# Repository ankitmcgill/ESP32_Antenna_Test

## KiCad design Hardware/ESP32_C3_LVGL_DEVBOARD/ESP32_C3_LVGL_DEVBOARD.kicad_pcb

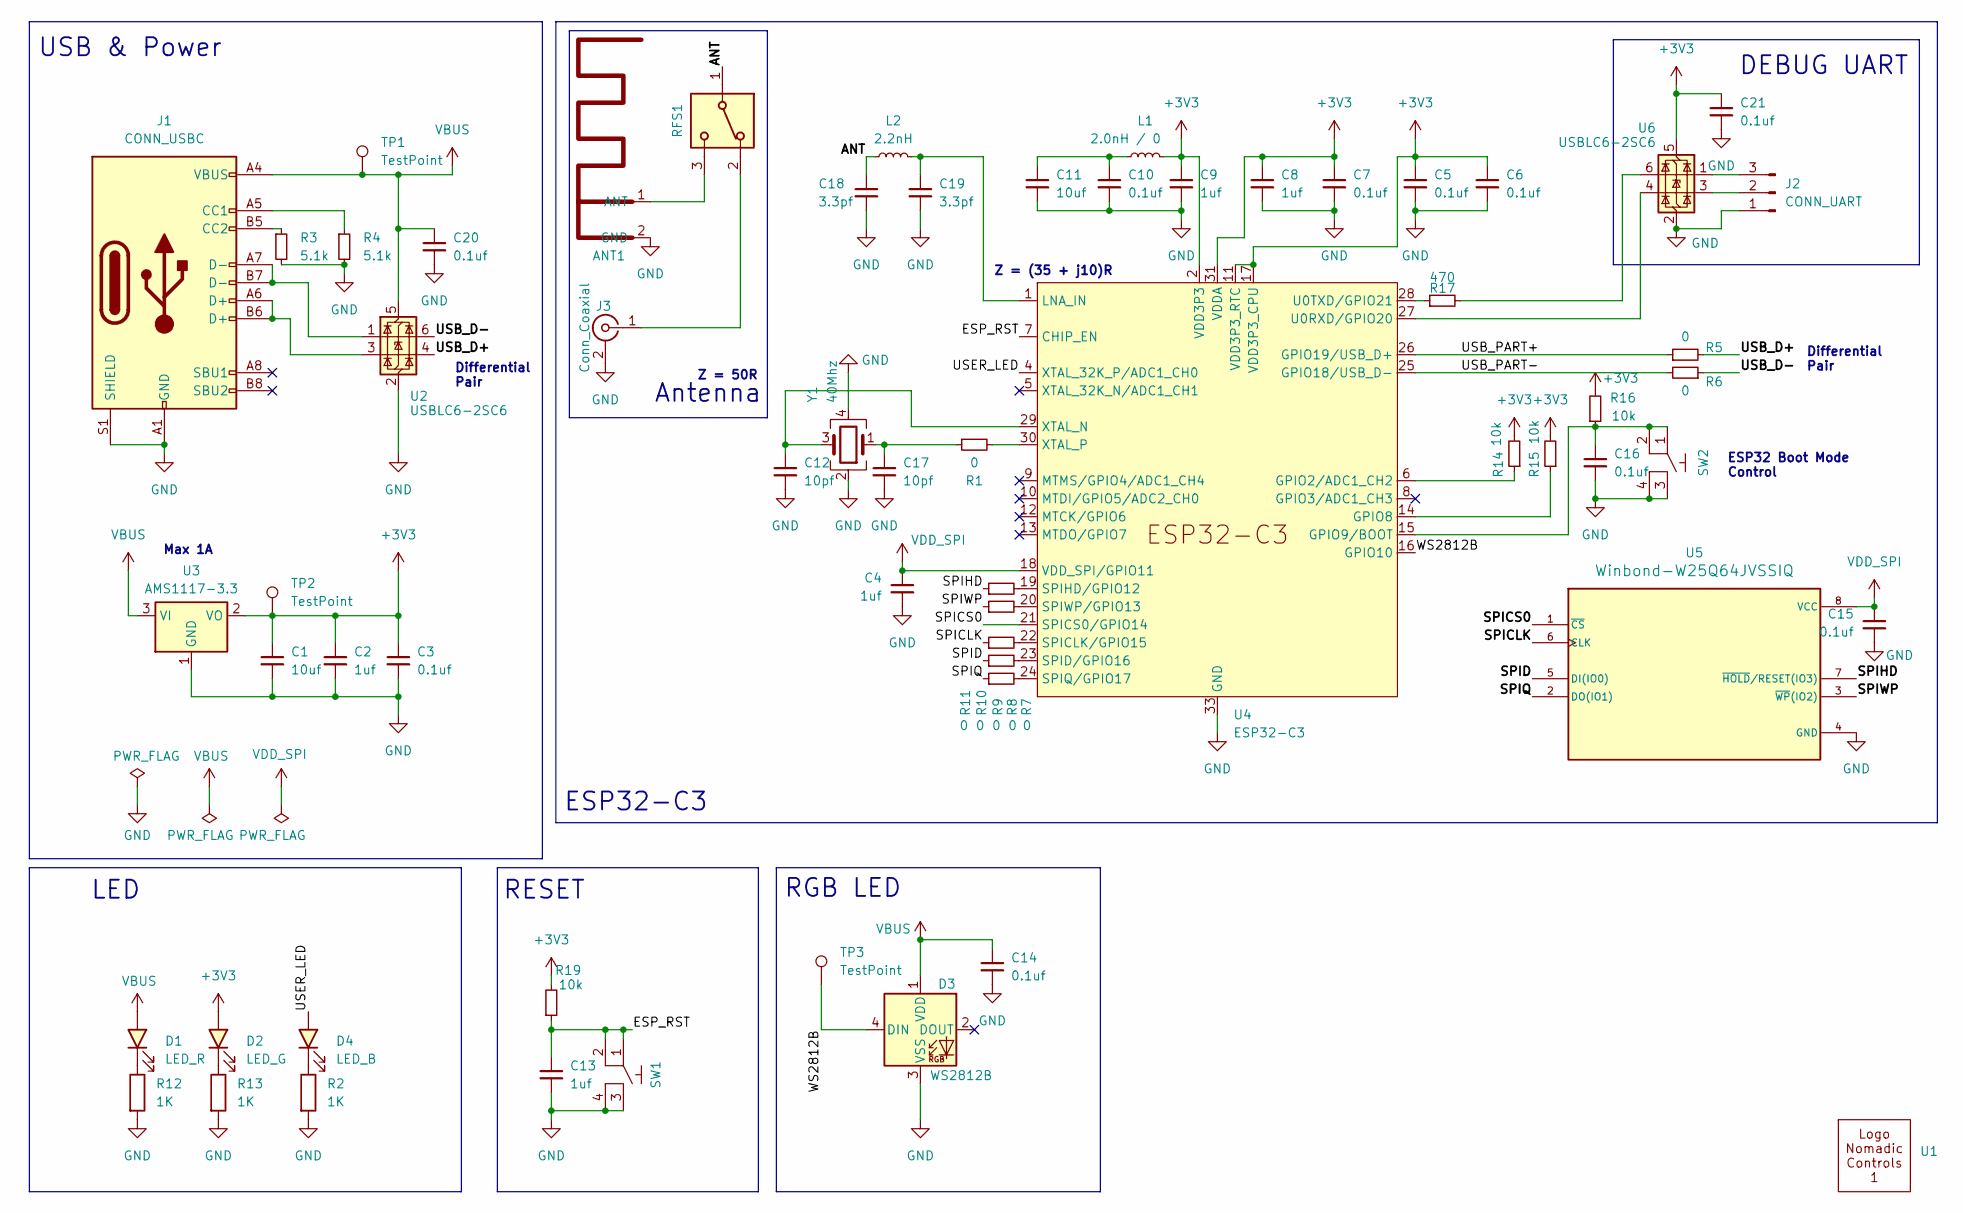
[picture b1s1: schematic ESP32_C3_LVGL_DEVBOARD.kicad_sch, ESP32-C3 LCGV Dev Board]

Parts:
ANT1: Texas_SWRA117D_2.4GHz_Left
C1: 10uf; CP_EIA-3216-18_Kemet-A
C2, C4, C8, C9, C13: 1uf; C_0805_2012Metric
C3, C5, C6, C7, C10, C14, C15, C16, C20, C21: 0.1uf; C_0603_1608Metric
C11: 10uf; C_0805_2012Metric
C12, C17: 10pf; C_0603_1608Metric
C18, C19: 3.3pf; C_0402_1005Metric
D1: LED_R; LED_0603_1608Metric
D2: LED_G; LED_0603_1608Metric
D3: WS2812B; LED_WS2812B-2020_PLCC4_2.0x2.0mm
D4: LED_B; LED_0603_1608Metric
J1: CONN_USBC; USB_C_Receptacle_GCT_USB4105-xx-A_16P_TopMnt_Horizontal
J2: CONN_UART; PinHeader_1x03_P1.27mm_Vertical
J3: Conn_Coaxial; U.FL_Molex_MCRF_73412-0110_Vertical
L1: 2.0nH / 0; L_0603_1608Metric
L2: 2.2nH; L_0402_1005Metric
R1, R5, R6, R7, R8, R9, R10, R11: 0; R_0603_1608Metric
R2, R12, R13: 1K; R_0603_1608Metric
R3, R4: 5.1k; R_0603_1608Metric
R14, R15, R16, R19: 10k; R_0603_1608Metric
R17: 470; R_0805_2012Metric
RFS1: RF Switch 0402 2Pos
SW1, SW2: SW_Push_SPST_4Pads; Tactile Microswitch 3x4x2.5mm
TP1, TP2, TP3: TestPoint; TestPoint_Pad_1.0x1.0mm
U1: Nomadic_Controls_Concise_2_5mm
U2, U6: USBLC6-2SC6; SOT-23-6
U3: AMS1117-3.3; SOT-223-3_TabPin2
U4: ESP32-C3; QFN-32-1EP_5x5mm_P0.5mm_EP3.45x3.45mm
U5: Winbond-W25Q64JVSSIQ; Winbond-SOIC-8_5P28X5P28_WIN
Y1: 40Mhz; Crystal_SMD_3225-4Pin_3.2x2.5mm

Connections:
+3V3: C1.1, C2.1, C3.1, C5.1, C6.1, C7.1, C8.1, C9.1, C21.1, D2.2 (A), L1.2, R14.2, R15.2, R16.2, R19.2, TP2.1, U3.2 (VO), U4.2 (VDD3P3), U4.3 (VDD3P3), U4.11 (VDD3P3_RTC), U4.17 (VDD3P3_CPU), U4.31 (VDDA), U4.32 (VDDA), U6.5 (VBUS)
/ANT: C18.1, L2.1, RFS1.1
/ESP_RST: C13.1, R19.1, SW1.1, SW1.2, U4.7 (CHIP_EN)
/SPICLK: R9.1, U5.6 (CLK)
/SPICS0: U4.21 (SPICS0/GPIO14), U5.1 (~CS)
/SPID: R10.1, U5.5 (DI(IO0))
/SPIHD: R7.1, U5.7 (~HOLD/RESET(IO3))
/SPIQ: R11.1, U5.2 (DO(IO1))
/SPIWP: R8.1, U5.3 (~WP(IO2))
/USB_D+: R5.2, U2.4 (I/O2)
/USB_D-: R6.1, U2.6 (I/O1)
/USB_PART+: R5.1, U4.26 (GPIO19/USB_D+)
/USB_PART-: R6.2, U4.25 (GPIO18/USB_D-)
/USER_LED: D4.2 (A), U4.4 (XTAL_32K_P/ADC1_CH0)
/WS2812B: D3.4 (DIN), TP3.1, U4.16 (GPIO10)
GND: ANT1.2 (GND), C1.2, C2.2, C3.2, C4.2, C5.2, C6.2, C7.2, C8.2, C9.2, C10.2, C11.2, C12.2, C13.2, C14.2, C15.2, C16.2, C17.2, C18.2, C19.2, C20.2, C21.2, D3.3 (VSS), J1.A1 (GND), J1.A12 (GND), J1.B1 (GND), J1.B12 (GND), J1.S1 (SHIELD), J2.1, J3.2 (Ext), R2.2, R3.2, R4.2, R12.2, R13.2, SW1.3, SW1.4, SW2.3, SW2.4, U2.2 (GND), U3.1 (GND), U4.33 (GND), U5.4 (GND), U6.2 (GND), Y1.2, Y1.4
unnamed: ANT1.1 (ANT), RFS1.3
unnamed: C10.1, C11.1, L1.1
unnamed: C17.1, R1.1, Y1.1
unnamed: D1.1 (K), R12.1
unnamed: D2.1 (K), R13.1
unnamed: D4.1 (K), R2.1
unnamed: J1.A5 (CC1), R4.1
unnamed: J1.B5 (CC2), R3.1
unnamed: J1.A6 (D+), J1.B6 (D+), U2.3 (I/O2)
unnamed: J1.A7 (D-), J1.B7 (D-), U2.1 (I/O1)
unnamed: J2.2, U6.3 (I/O2)
unnamed: J2.3, U6.1 (I/O1)
unnamed: J3.1 (In), RFS1.2
unnamed: R17.2, U6.6 (I/O1)
unnamed: R14.1, U4.6 (GPIO2/ADC1_CH2)
unnamed: R15.1, U4.14 (GPIO8)
unnamed: C16.1, R16.1, SW2.1, SW2.2, U4.15 (GPIO9/BOOT)
unnamed: C19.1, L2.2, U4.1 (LNA_IN)
unnamed: R9.2, U4.22 (SPICLK/GPIO15)
unnamed: R10.2, U4.23 (SPID/GPIO16)
unnamed: R7.2, U4.19 (SPIHD/GPIO12)
unnamed: R11.2, U4.24 (SPIQ/GPIO17)
unnamed: R8.2, U4.20 (SPIWP/GPIO13)
unnamed: U4.27 (U0RXD/GPIO20), U6.4 (I/O2)
unnamed: R17.1, U4.28 (U0TXD/GPIO21)
unnamed: C12.1, U4.29 (XTAL_N), Y1.3
unnamed: R1.2, U4.30 (XTAL_P)
VBUS: C14.1, C20.1, D1.2 (A), D3.1 (VDD), J1.A4 (VBUS), J1.A9 (VBUS), J1.B4 (VBUS), J1.B9 (VBUS), TP1.1, U2.5 (VBUS), U3.3 (VI)
VDD_SPI: C4.1, C15.1, U4.18 (VDD_SPI/GPIO11), U5.8 (VCC)

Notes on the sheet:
Z = (35 + j10)R
DEBUG UART
Differential Pair
ESP32-C3
ESP32 Boot Mode Control
RGB LED
USB & Power
LED
Antenna
Max 1A
RESET
Z = 50R

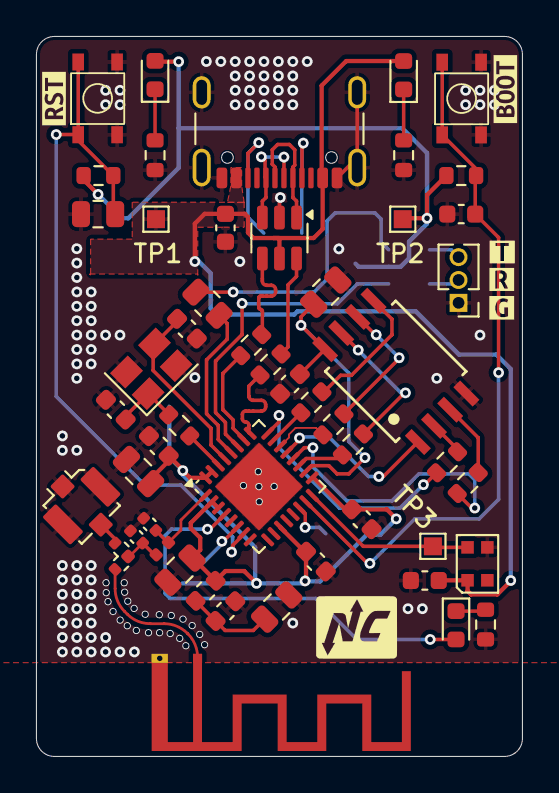
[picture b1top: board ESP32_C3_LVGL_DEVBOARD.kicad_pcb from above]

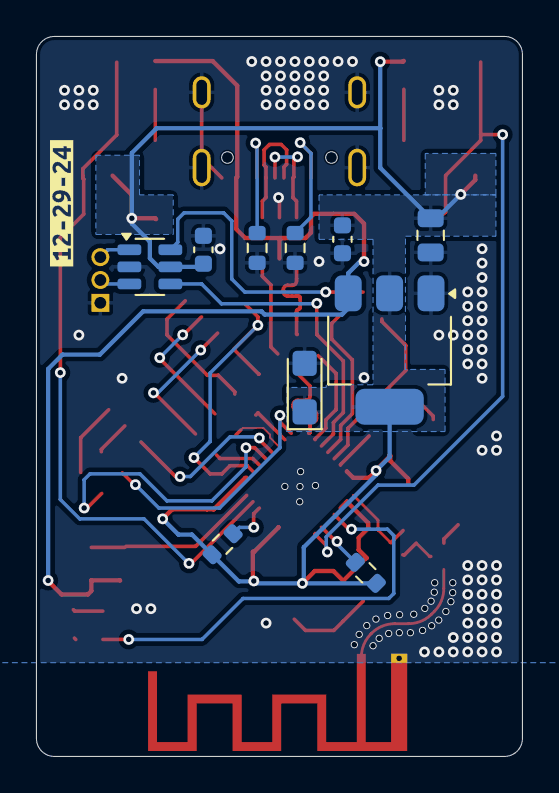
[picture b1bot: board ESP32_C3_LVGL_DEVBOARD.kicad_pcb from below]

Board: 4 copper layers, 27.0 x 40.0 mm, 68 parts (11 on the bottom side), 45 nets.

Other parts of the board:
kibuzzard-676F80CA: G***; kibuzzard-676F80CA
kibuzzard-676F8115: G***; kibuzzard-676F8115
kibuzzard-6771D0B9: G***; kibuzzard-6771D0B9
kibuzzard-6779637F: G***; kibuzzard-6779637F
kibuzzard-67796362: G***; kibuzzard-67796362
kibuzzard-67796372: G***; kibuzzard-67796372

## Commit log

2025-01-02 added hardware files
2025-01-02 updated pcb build up details
2025-01-04 updated pcb with placement & basic routing
2025-01-05 kicad project update
2025-01-06 pcb commit
2025-01-06 pcb project update
2025-01-06 updated pcb + gerbers+ drills
2025-01-06 kicad pcb committ
2025-01-06 pcb committ
2025-01-08 pcb committ + ibom
